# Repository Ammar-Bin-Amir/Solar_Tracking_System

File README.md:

# Solar Tracking System

The main objective of the project is to harness maximum amount of sunlight from sun and convert it into electricity. This can be done by aligning the solar panel perpendicular to sun rays so that maximum sunlight can be converted into electrical energy.

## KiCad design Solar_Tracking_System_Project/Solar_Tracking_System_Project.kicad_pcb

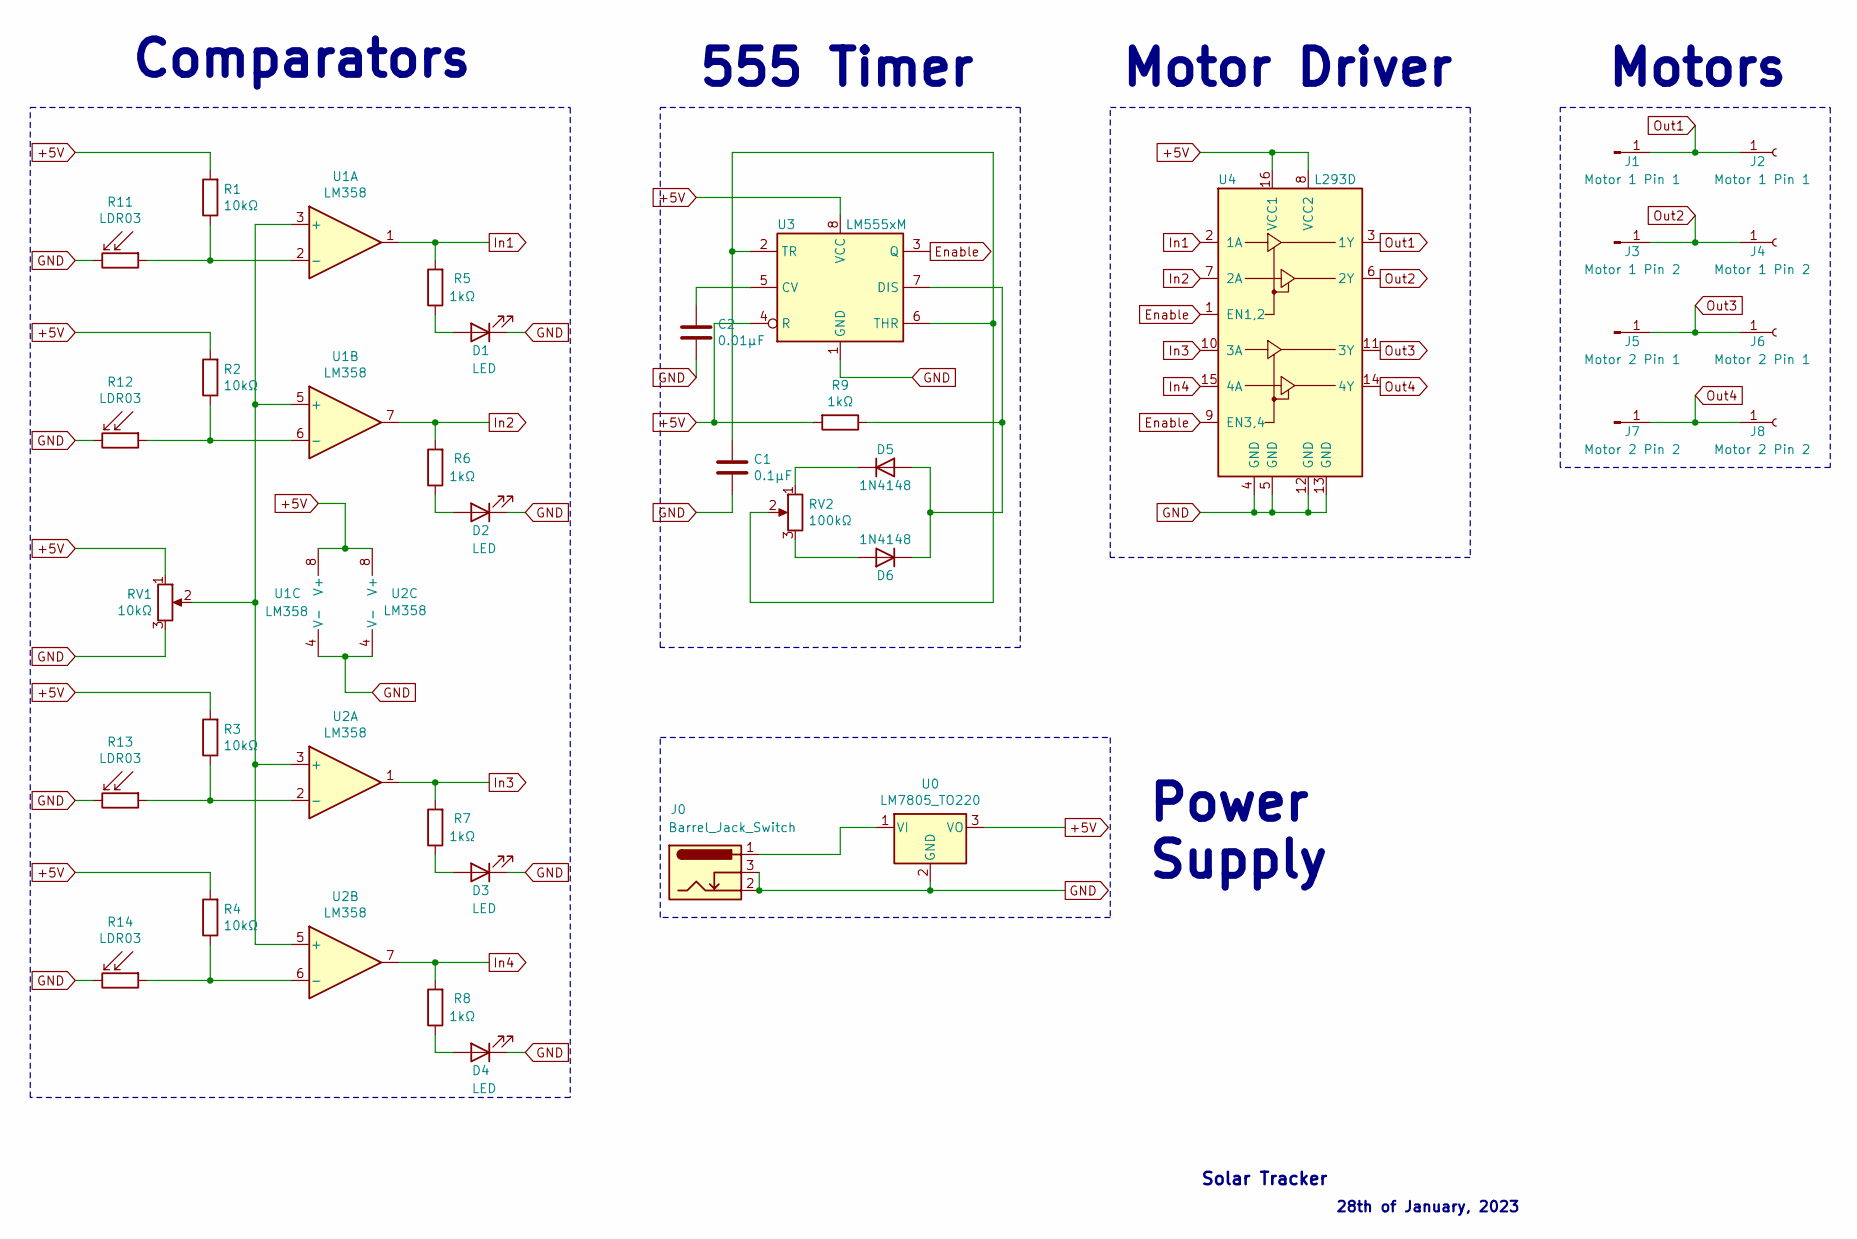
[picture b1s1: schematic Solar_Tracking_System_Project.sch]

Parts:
C1: 0.1μF; C_Disc_D5.0mm_W2.5mm_P5.00mm
C2: 0.01μF; C_Disc_D5.0mm_W2.5mm_P2.50mm
D1, D2, D3, D4: LED; LED_D5.0mm_Clear
D5, D6: 1N4148; D_DO-35_SOD27_P7.62mm_Horizontal
J0: Barrel_Jack_Switch; BarrelJack_Horizontal
J1: Motor 1 Pin 1; PinHeader_1x01_P2.54mm_Vertical
J2: Motor 1 Pin 1; PinSocket_1x01_P2.54mm_Vertical
J3: Motor 1 Pin 2; PinHeader_1x01_P2.54mm_Vertical
J4: Motor 1 Pin 2; PinSocket_1x01_P2.54mm_Vertical
J5: Motor 2 Pin 1; PinHeader_1x01_P2.54mm_Vertical
J6: Motor 2 Pin 1; PinSocket_1x01_P2.54mm_Vertical
J7: Motor 2 Pin 2; PinHeader_1x01_P2.54mm_Vertical
J8: Motor 2 Pin 2; PinSocket_1x01_P2.54mm_Vertical
R1, R2, R3, R4: 10kΩ; R_Axial_DIN0207_L6.3mm_D2.5mm_P15.24mm_Horizontal
R5, R6, R7, R8, R9: 1kΩ; R_Axial_DIN0207_L6.3mm_D2.5mm_P15.24mm_Horizontal
R11, R12, R13, R14: LDR03; R_LDR_10x8.5mm_P7.6mm_Vertical
RV1: 10kΩ; Potentiometer_ACP_CA9-H3,8_Horizontal
RV2: 100kΩ; Potentiometer_ACP_CA9-H3,8_Horizontal
U0: LM7805_TO220; TO-220-3_Vertical
U1, U2: LM358; DIP-8_W7.62mm_Socket_LongPads
U3: LM555xM; DIP-8_W7.62mm_Socket_LongPads
U4: L293D; DIP-16_W7.62mm_Socket_LongPads

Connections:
+5V: R1.2, R2.2, R3.2, R4.2, R9.2, RV1.1, U0.3 (VO), U1.8 (V+), U2.8 (V+), U3.4 (R), U3.8 (VCC), U4.8 (VCC2), U4.16 (VCC1)
Enable: U3.3 (Q), U4.1 (EN1,2), U4.9 (EN3,4)
GND: C1.2, C2.2, D1.1 (K), D2.1 (K), D3.1 (K), D4.1 (K), J0.2, J0.3, R11.2, R12.2, R13.2, R14.2, RV1.3, U0.2 (GND), U1.4 (V-), U2.4 (V-), U3.1 (GND), U4.4 (GND), U4.5 (GND), U4.12 (GND), U4.13 (GND)
In1: R5.2, U1.1, U4.2 (1A)
In2: R6.2, U1.7, U4.7 (2A)
In3: R7.2, U2.1, U4.10 (3A)
In4: R8.2, U2.7, U4.15 (4A)
unnamed: C1.1, RV2.2, U3.2 (TR), U3.6 (THR)
unnamed: C2.1, U3.5 (CV)
unnamed: D1.2 (A), R5.1
unnamed: D2.2 (A), R6.1
unnamed: D3.2 (A), R7.1
unnamed: D4.2 (A), R8.1
unnamed: D5.1 (K), RV2.1
unnamed: D5.2 (A), D6.1 (K), R9.1, U3.7 (DIS)
unnamed: D6.2 (A), RV2.3
unnamed: J0.1, U0.1 (VI)
unnamed: R1.1, R11.1, U1.2 (-)
unnamed: R2.1, R12.1, U1.6 (-)
unnamed: R3.1, R13.1, U2.2 (-)
unnamed: R4.1, R14.1, U2.6 (-)
unnamed: RV1.2, U1.3 (+), U1.5 (+), U2.3 (+), U2.5 (+)
Out1: J1.1, J2.1, U4.3 (1Y)
Out2: J3.1, J4.1, U4.6 (2Y)
Out3: J5.1, J6.1, U4.11 (3Y)
Out4: J7.1, J8.1, U4.14 (4Y)

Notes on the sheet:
28th of January, 2023
Solar Tracker
555 Timer
Comparators
Motor Driver
Power Supply
Motors

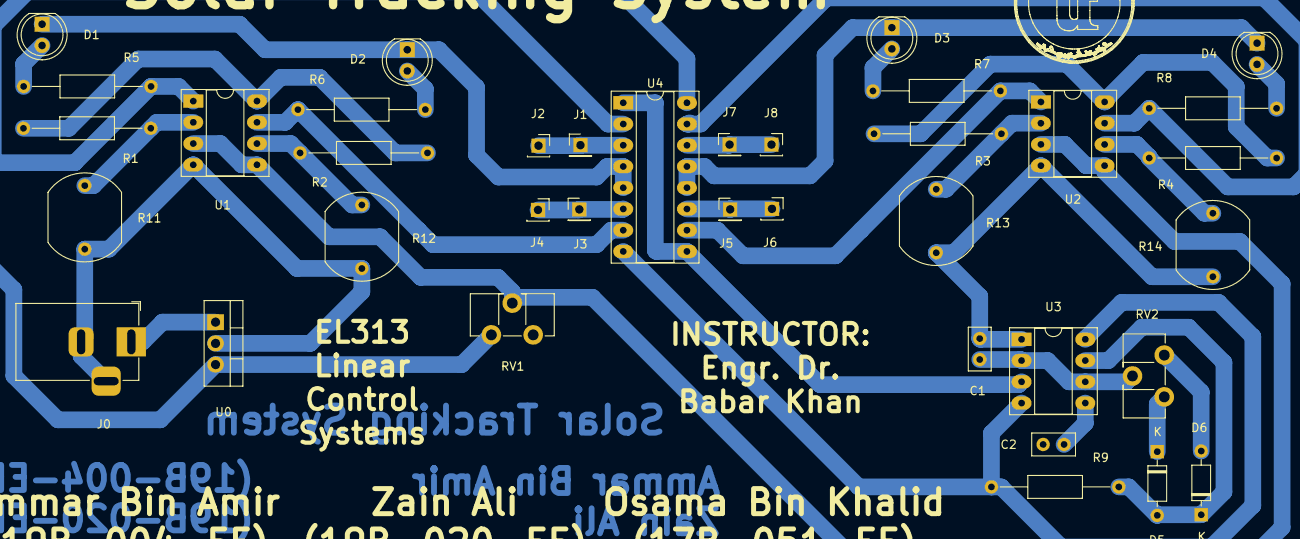
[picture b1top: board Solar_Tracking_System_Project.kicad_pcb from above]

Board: 2 copper layers, 37 parts (0 on the bottom side), 26 nets.
